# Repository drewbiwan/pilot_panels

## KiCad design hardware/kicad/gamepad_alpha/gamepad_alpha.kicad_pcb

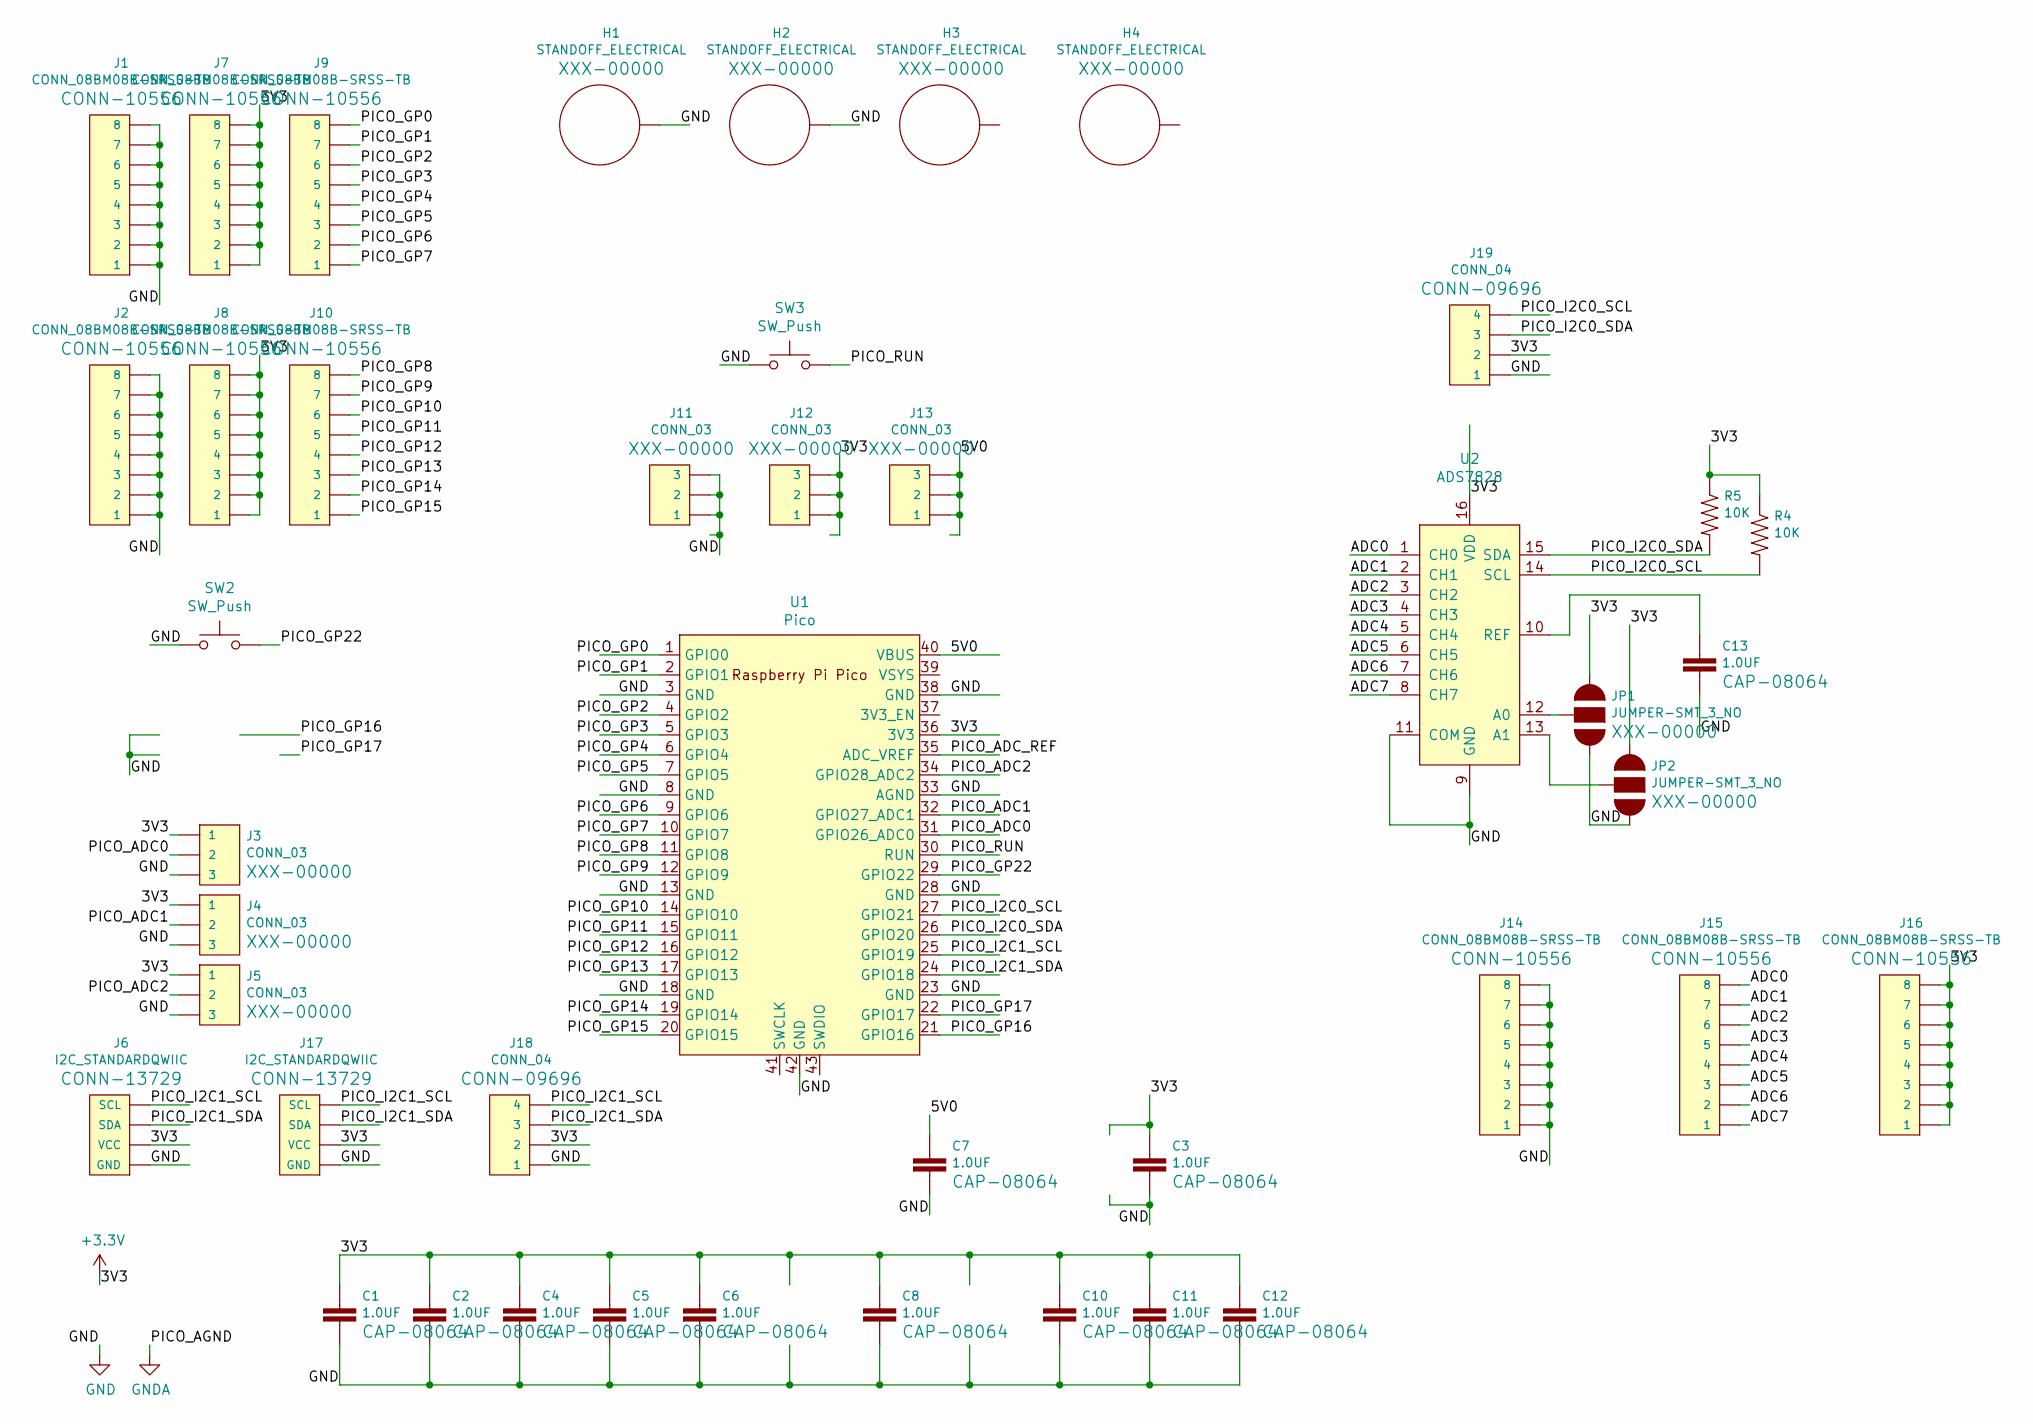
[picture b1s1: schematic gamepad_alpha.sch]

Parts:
C1, C2, C3, C4, C5, C6, C7, C8, C10, C11, C12, C13: 1.0UF; R_0805_2012Metric_Pad1.20x1.40mm_HandSolder
H1, H2, H3, H4: STANDOFF_ELECTRICAL; STANDOFF-ELECTRICAL
J1, J2, J7, J8, J9, J10, J14, J15, J16: CONN_08BM08B-SRSS-TB; PinHeader_1x08_P2.54mm_Vertical
J3, J4, J5, J11, J12, J13: CONN_03; 1X03
J6, J17: I2C_STANDARDQWIIC; 1X04_1MM_RA
J18, J19: CONN_04; 1X04
JP1, JP2: JUMPER-SMT_3_NO; SMT-JUMPER_3_NO_SILK
R4, R5: 10K; R_0805_2012Metric_Pad1.20x1.40mm_HandSolder
SW2, SW3: SW_Push; SW_SPST_TL3342
U1: Pico; RPi_Pico_SMD_TH
U2: ADS7828; TSSOP-16_4.4x5mm_P0.65mm

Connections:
+3V3: C1.1, C2.1, C3.1, C4.1, C5.1, C6.1, C8.1, C10.1, C11.1, C12.1, J3.1, J4.1, J5.1, J6.2 (VCC), J7.1, J7.2, J7.3, J7.4, J7.5, J7.6, J7.7, J7.8, J8.1, J8.2, J8.3, J8.4, J8.5, J8.6, J8.7, J8.8, J12.1, J12.2, J12.3, J16.1, J16.2, J16.3, J16.4, J16.5, J16.6, J16.7, J16.8, J17.2 (VCC), J18.2, J19.2, JP1.1, JP2.1, R4.1, R5.1, U1.36 (3V3), U2.16 (VDD)
/5V0: C7.1, J13.1, J13.2, J13.3, U1.40 (VBUS)
/ADC0: J15.8, U2.1 (CH0)
/ADC1: J15.7, U2.2 (CH1)
/ADC2: J15.6, U2.3 (CH2)
/ADC3: J15.5, U2.4 (CH3)
/ADC4: J15.4, U2.5 (CH4)
/ADC5: J15.3, U2.6 (CH5)
/ADC6: J15.2, U2.7 (CH6)
/ADC7: J15.1, U2.8 (CH7)
/PICO_ADC0: J3.2, U1.31 (GPIO26_ADC0)
/PICO_ADC1: J4.2, U1.32 (GPIO27_ADC1)
/PICO_ADC2: J5.2, U1.34 (GPIO28_ADC2)
/PICO_ADC_REF: U1.35 (ADC_VREF)
/PICO_GP0: J9.8, U1.1 (GPIO0)
/PICO_GP1: J9.7, U1.2 (GPIO1)
/PICO_GP2: J9.6, U1.4 (GPIO2)
/PICO_GP3: J9.5, U1.5 (GPIO3)
/PICO_GP4: J9.4, U1.6 (GPIO4)
/PICO_GP5: J9.3, U1.7 (GPIO5)
/PICO_GP6: J9.2, U1.9 (GPIO6)
/PICO_GP7: J9.1, U1.10 (GPIO7)
/PICO_GP8: J10.8, U1.11 (GPIO8)
/PICO_GP9: J10.7, U1.12 (GPIO9)
/PICO_GP10: J10.6, U1.14 (GPIO10)
/PICO_GP11: J10.5, U1.15 (GPIO11)
/PICO_GP12: J10.4, U1.16 (GPIO12)
/PICO_GP13: J10.3, U1.17 (GPIO13)
/PICO_GP14: J10.2, U1.19 (GPIO14)
/PICO_GP15: J10.1, U1.20 (GPIO15)
/PICO_GP16: U1.21 (GPIO16)
/PICO_GP17: U1.22 (GPIO17)
/PICO_GP22: SW2.2, U1.29 (GPIO22)
/PICO_I2C0_SCL: J19.4, R4.2, U1.27 (GPIO21), U2.14 (SCL)
/PICO_I2C0_SDA: J19.3, R5.2, U1.26 (GPIO20), U2.15 (SDA)
/PICO_I2C1_SCL: J6.4 (SCL), J17.4 (SCL), J18.4, U1.25 (GPIO19)
/PICO_I2C1_SDA: J6.3 (SDA), J17.3 (SDA), J18.3, U1.24 (GPIO18)
/PICO_RUN: SW3.2, U1.30 (RUN)
GND: C1.2, C2.2, C3.2, C4.2, C5.2, C6.2, C7.2, C8.2, C10.2, C11.2, C12.2, C13.2, H1.P1, H2.P1, J1.1, J1.2, J1.3, J1.4, J1.5, J1.6, J1.7, J1.8, J2.1, J2.2, J2.3, J2.4, J2.5, J2.6, J2.7, J2.8, J3.3, J4.3, J5.3, J6.1 (GND), J11.1, J11.2, J11.3, J14.1, J14.2, J14.3, J14.4, J14.5, J14.6, J14.7, J14.8, J17.1 (GND), J18.1, J19.1, JP1.3, JP2.3, SW2.1, SW3.1, U1.3 (GND), U1.8 (GND), U1.13 (GND), U1.18 (GND), U1.23 (GND), U1.28 (GND), U1.33 (AGND), U1.38 (GND), U1.42 (GND), U2.9 (GND), U2.11 (COM)
unnamed: C13.1, U2.10 (REF)
unnamed: JP1.2, U2.12 (A0)
unnamed: JP2.2, U2.13 (A1)

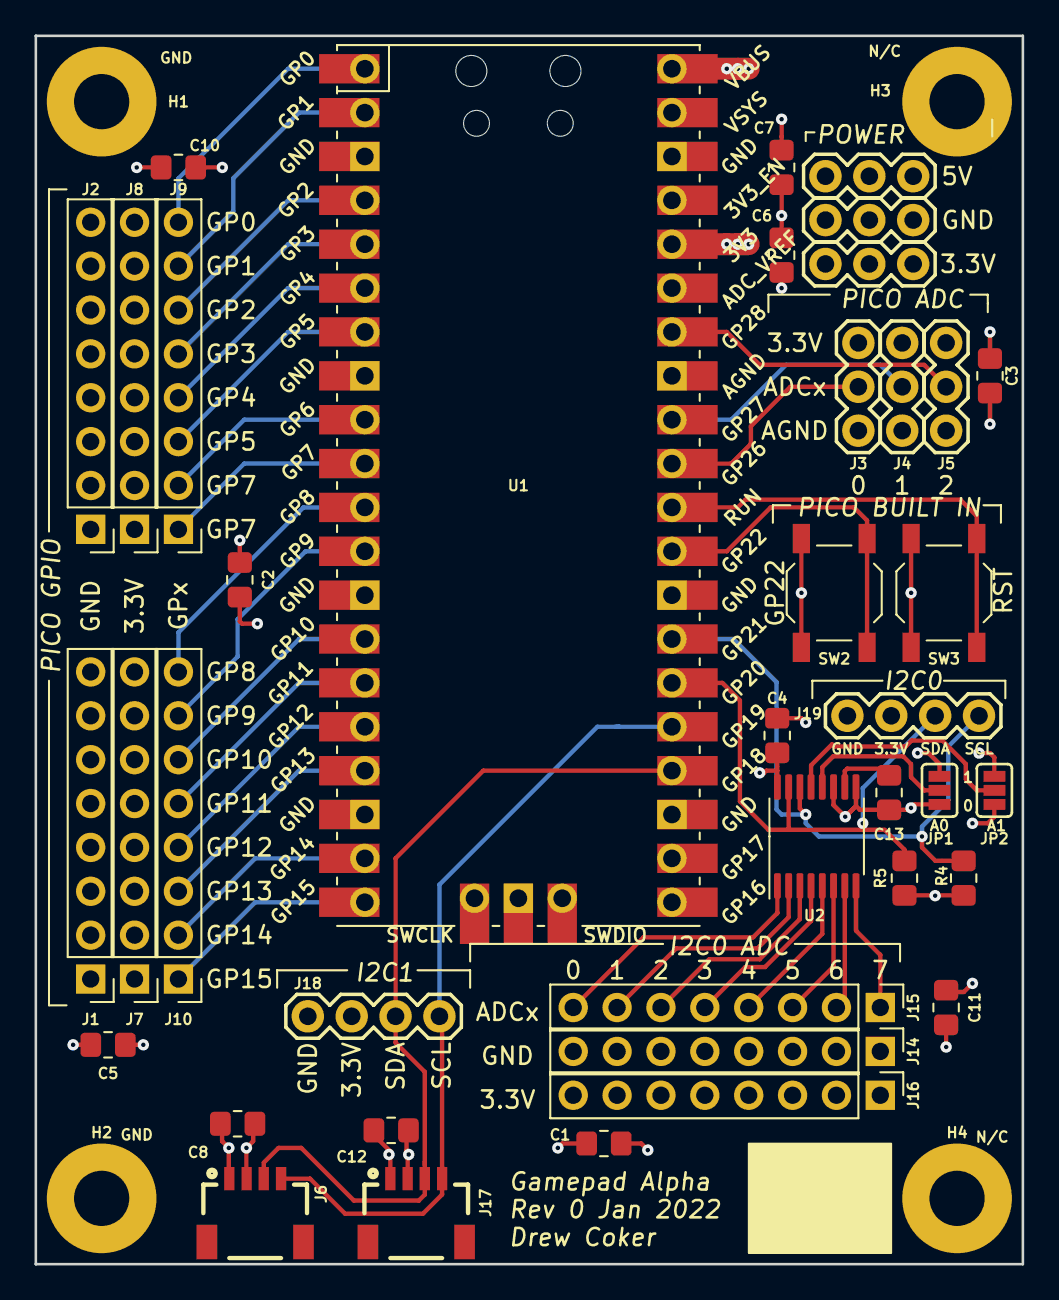
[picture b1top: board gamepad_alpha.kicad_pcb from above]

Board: 4 copper layers, 57.2 x 71.1 mm, 43 parts (0 on the bottom side), 39 nets.

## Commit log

2022-01-23 Added script for deploying to hardware
2022-01-23 added documentation
2022-01-23 playing around with hardware, code structure
2022-01-24 Added neopixels. Tested HID successfully
2022-01-27 clearer hid map
2022-01-29 Ad mod file for rev0
2022-01-30 composite hid device setup, not working
2022-01-30 still tyring
2022-01-30 "report id declaration outside of collection"
2022-01-30 working with separate reports for buttons and axes
2022-01-30 Added sliders to analog report
2022-02-25 Added new directory for alpha rev 0 hardware
2022-02-27 more reference pictures, uf2 for pico
2022-02-27 moved examples, uf2, library directories
2022-02-27 Actually moved things
2022-03-02 removed all feather-specific code
2022-03-02 some changes are needed for rev1
2022-03-02 i2c pullup issue found
2022-03-02 added i2c interface, pin strings
2022-03-02 Updated report, moving to generic configuration settings
2022-05-01 Adding reference materials
2022-05-02 Reorganized digital io setup and read
